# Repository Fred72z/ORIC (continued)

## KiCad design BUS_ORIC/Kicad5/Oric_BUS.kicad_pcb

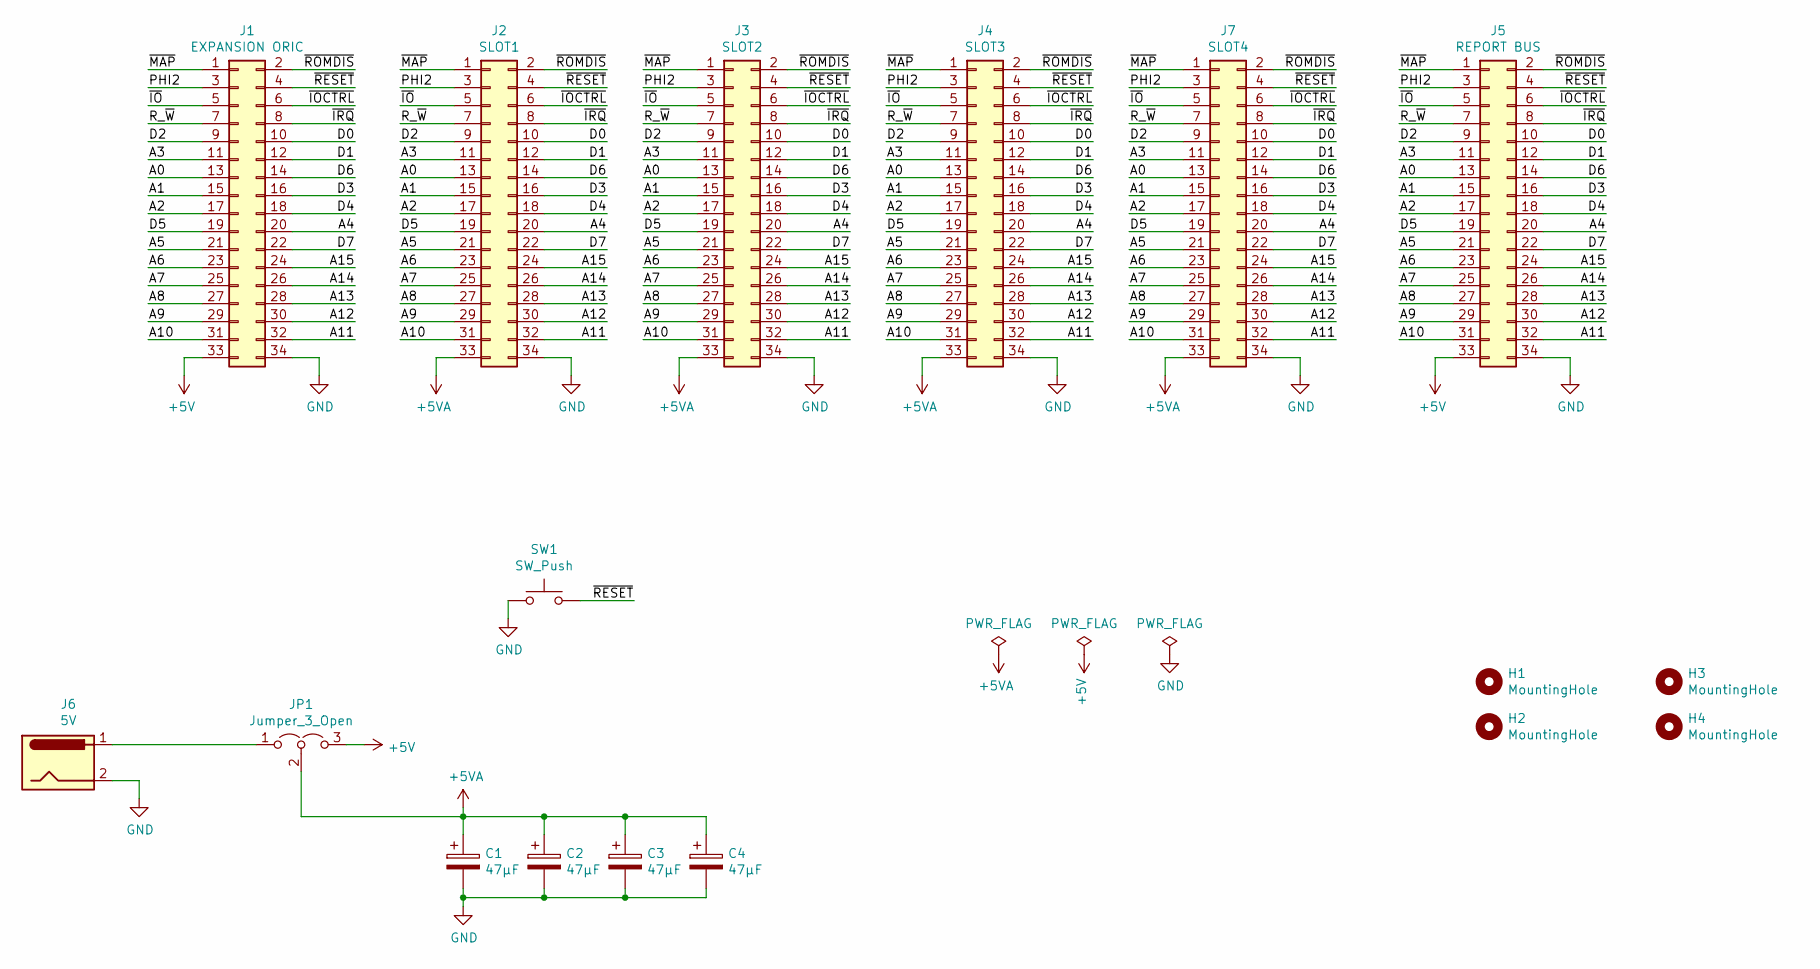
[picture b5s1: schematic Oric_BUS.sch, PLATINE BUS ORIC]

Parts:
C1, C2, C3, C4: 47µF; CP_Radial_D5.0mm_P2.00mm_Horizontal
H1, H2, H3, H4: MountingHole; MountingHole_3.2mm_M3
J1: EXPANSION ORIC; IDC-Header_2x17_P2.54mm_Vertical
J2: SLOT1; PinSocket_2x17_P2.54mm_Vertical
J3: SLOT2; PinSocket_2x17_P2.54mm_Vertical
J4: SLOT3; PinSocket_2x17_P2.54mm_Vertical
J5: REPORT BUS; IDC-Header_2x17_P2.54mm_Vertical
J6: 5V; BarrelJack_Horizontal
J7: SLOT4; PinSocket_2x17_P2.54mm_Vertical
JP1: Jumper_3_Open; PinHeader_1x03_P2.54mm_Vertical
SW1: SW_Push; SW_Tactile_SPST_Angled_PTS645Vx39-2LFS

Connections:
+5V: J1.33, J5.33, JP1.3 (B)
+5VA: C1.1, C2.1, C3.1, C4.1, J2.33, J3.33, J4.33, J7.33, JP1.2 (C)
/A0: J1.13, J2.13, J3.13, J4.13, J5.13, J7.13
/A1: J1.15, J2.15, J3.15, J4.15, J5.15, J7.15
/A2: J1.17, J2.17, J3.17, J4.17, J5.17, J7.17
/A3: J1.11, J2.11, J3.11, J4.11, J5.11, J7.11
/A4: J1.20, J2.20, J3.20, J4.20, J5.20, J7.20
/A5: J1.21, J2.21, J3.21, J4.21, J5.21, J7.21
/A6: J1.23, J2.23, J3.23, J4.23, J5.23, J7.23
/A7: J1.25, J2.25, J3.25, J4.25, J5.25, J7.25
/A8: J1.27, J2.27, J3.27, J4.27, J5.27, J7.27
/A9: J1.29, J2.29, J3.29, J4.29, J5.29, J7.29
/A10: J1.31, J2.31, J3.31, J4.31, J5.31, J7.31
/A11: J1.32, J2.32, J3.32, J4.32, J5.32, J7.32
/A12: J1.30, J2.30, J3.30, J4.30, J5.30, J7.30
/A13: J1.28, J2.28, J3.28, J4.28, J5.28, J7.28
/A14: J1.26, J2.26, J3.26, J4.26, J5.26, J7.26
/A15: J1.24, J2.24, J3.24, J4.24, J5.24, J7.24
/D0: J1.10, J2.10, J3.10, J4.10, J5.10, J7.10
/D1: J1.12, J2.12, J3.12, J4.12, J5.12, J7.12
/D2: J1.9, J2.9, J3.9, J4.9, J5.9, J7.9
/D3: J1.16, J2.16, J3.16, J4.16, J5.16, J7.16
/D4: J1.18, J2.18, J3.18, J4.18, J5.18, J7.18
/D5: J1.19, J2.19, J3.19, J4.19, J5.19, J7.19
/D6: J1.14, J2.14, J3.14, J4.14, J5.14, J7.14
/D7: J1.22, J2.22, J3.22, J4.22, J5.22, J7.22
/PHI2: J1.3, J2.3, J3.3, J4.3, J5.3, J7.3
/R_~W: J1.7, J2.7, J3.7, J4.7, J5.7, J7.7
/~IO: J1.5, J2.5, J3.5, J4.5, J5.5, J7.5
/~IOCTRL: J1.6, J2.6, J3.6, J4.6, J5.6, J7.6
/~IRQ: J1.8, J2.8, J3.8, J4.8, J5.8, J7.8
/~MAP: J1.1, J2.1, J3.1, J4.1, J5.1, J7.1
/~RESET: J1.4, J2.4, J3.4, J4.4, J5.4, J7.4, SW1.2
/~ROMDIS: J1.2, J2.2, J3.2, J4.2, J5.2, J7.2
GND: C1.2, C2.2, C3.2, C4.2, J1.34, J2.34, J3.34, J4.34, J5.34, J6.2, J7.34, SW1.1
unnamed: J6.1, JP1.1 (A)

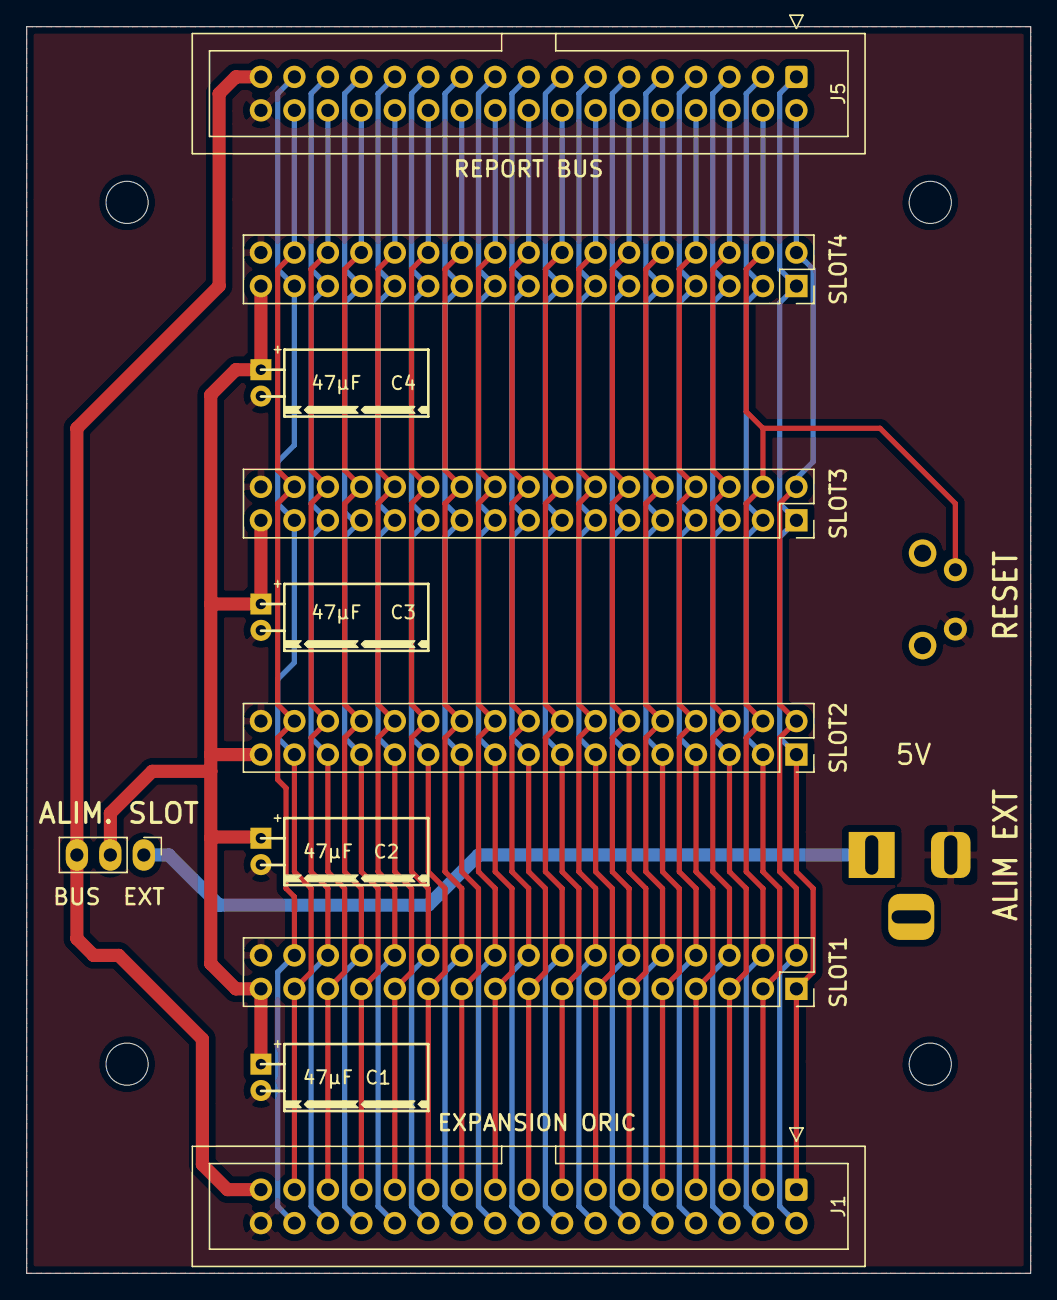
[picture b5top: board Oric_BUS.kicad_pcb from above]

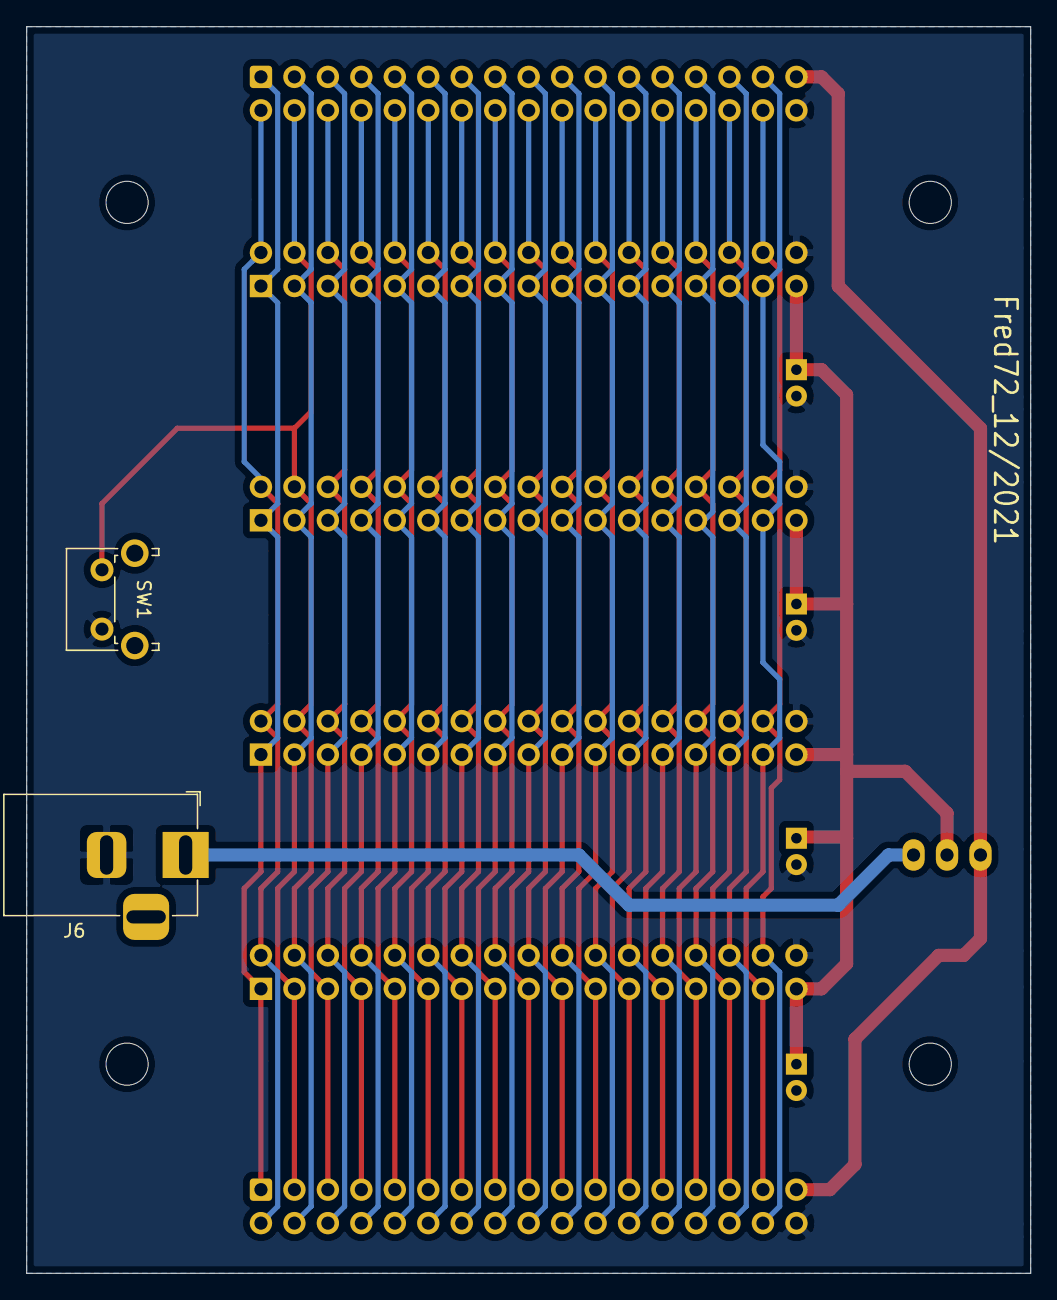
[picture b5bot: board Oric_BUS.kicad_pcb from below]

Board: 2 copper layers, 76.2 x 94.6 mm, 17 parts (2 on the bottom side), 36 nets.

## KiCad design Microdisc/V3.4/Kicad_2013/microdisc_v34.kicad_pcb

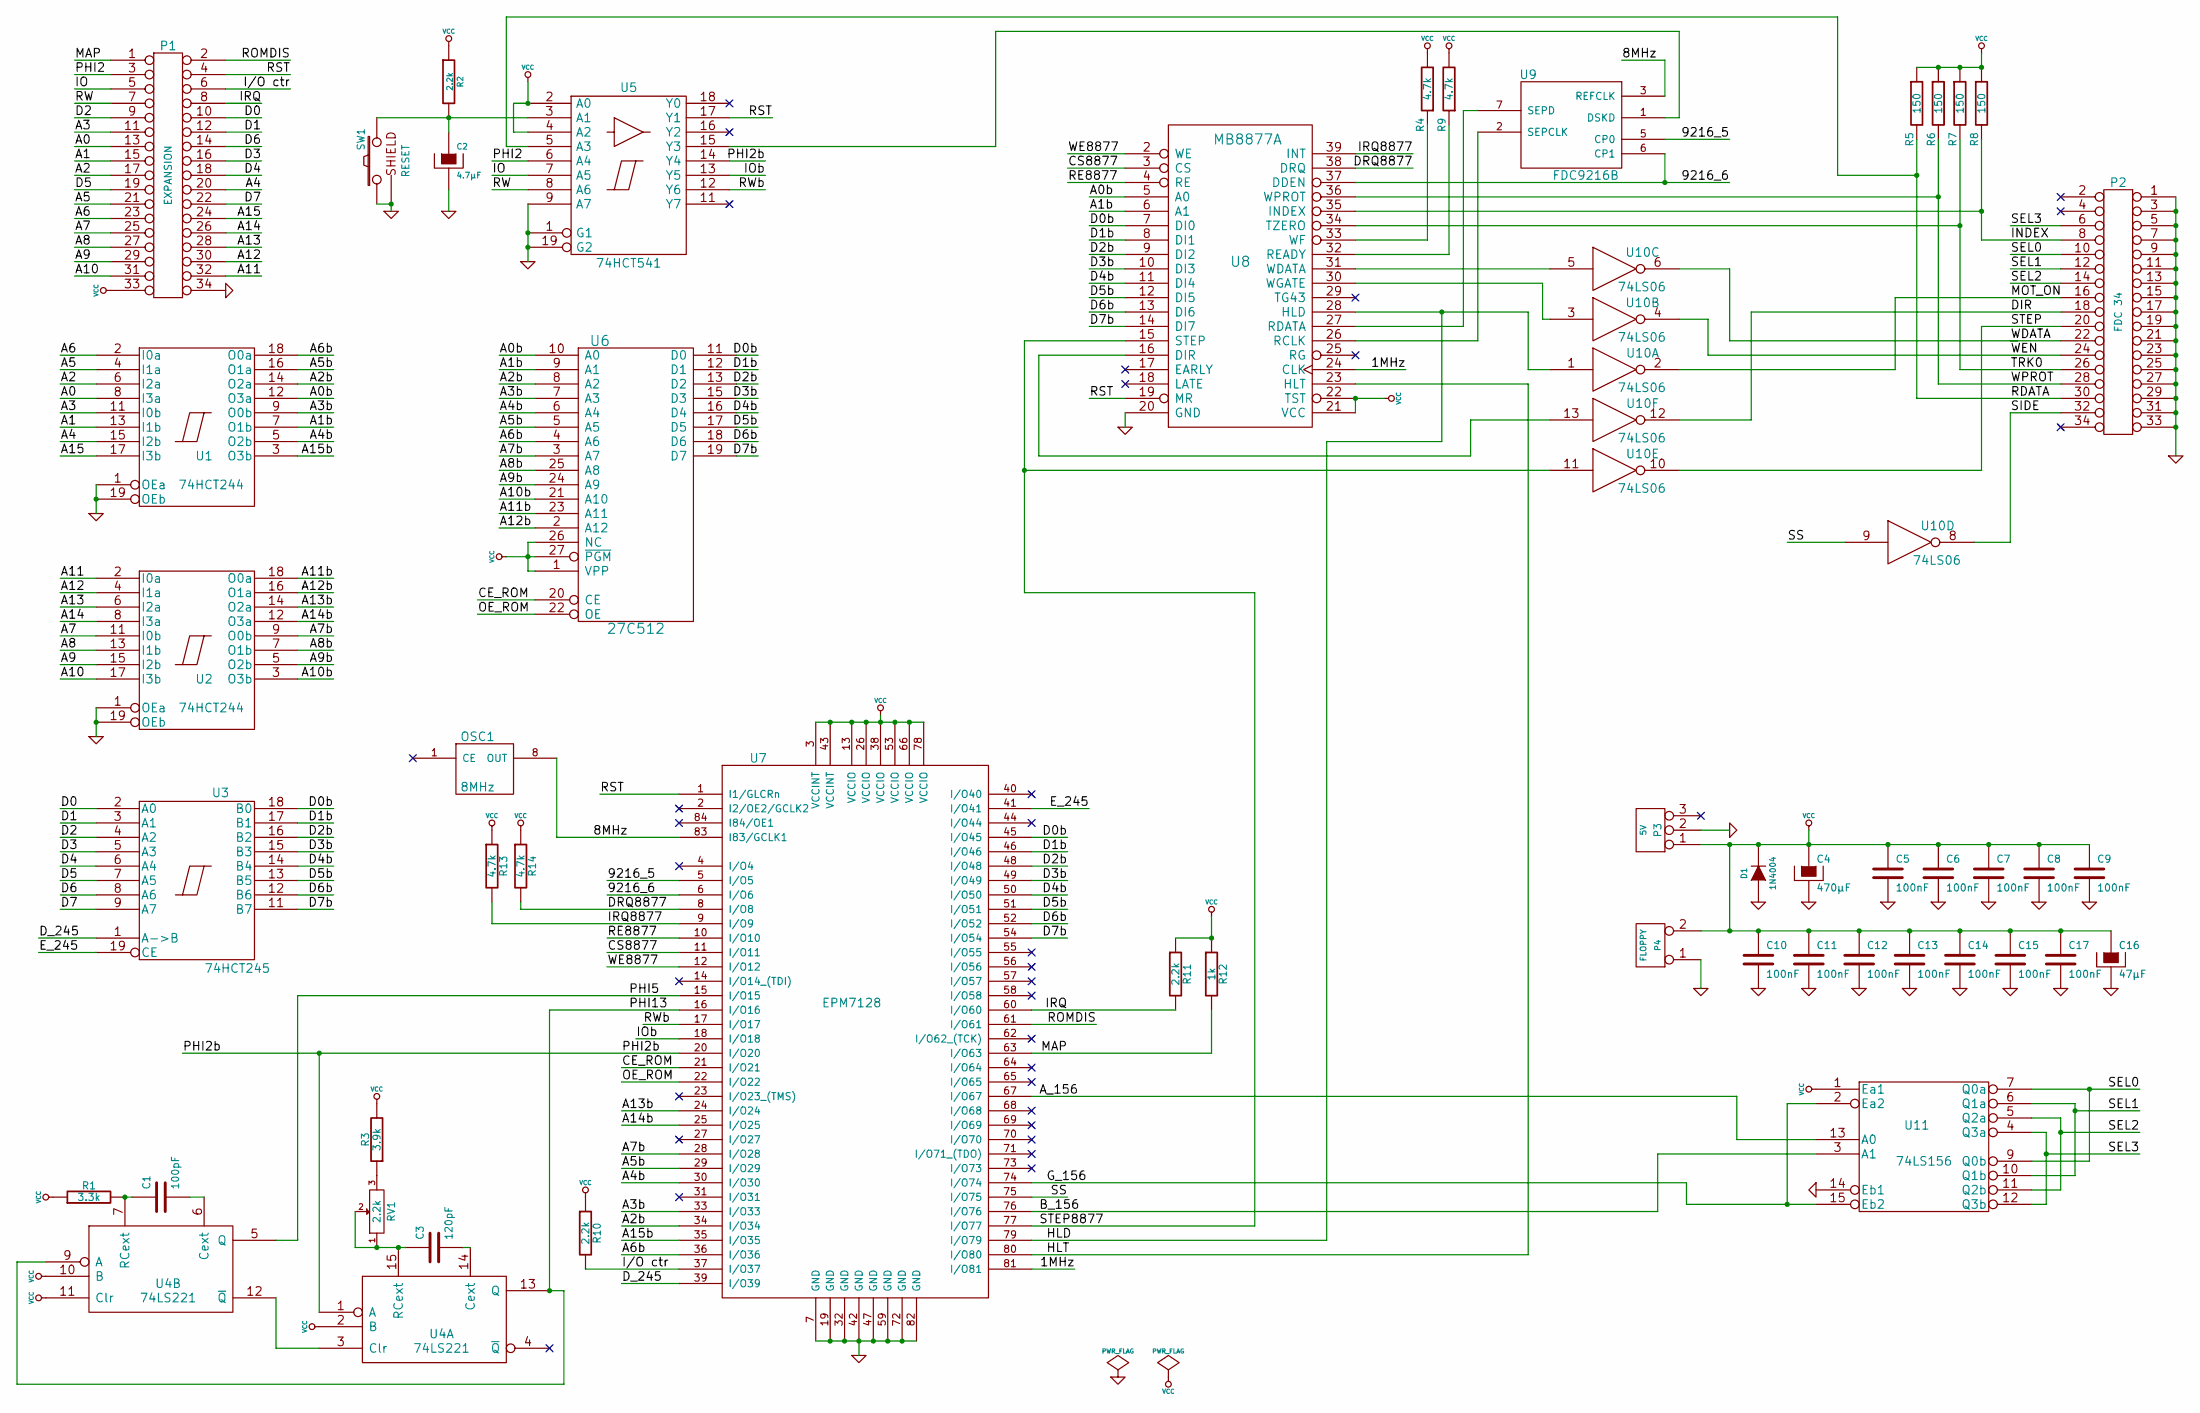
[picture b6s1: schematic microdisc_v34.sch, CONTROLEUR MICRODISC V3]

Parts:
C1: 100pF
C2: 4.7µF
C3: 120pF
C4: 470µF
C5, C6, C7, C8, C9, C10, C11, C12, C13, C14, C15, C17: 100nF
C16: 47µF
D1: 1N4004
OSC1: 8MHz
P1: EXPANSION
P2: FDC 34
P3: 5V
P4: FLOPPY
R1: 3.3k
R2, R10, R11: 2.2k
R3: 3.9k
R4, R9, R13, R14: 4.7k
R5, R6, R7, R8: 150
R12: 1k
RV1: 2.2k
SW1: RESET
U1, U2: 74HCT244
U3: 74HCT245
U4: 74LS221
U5: 74HCT541
U6: 27C512
U7: EPM7128
U8: MB8877A
U9: FDC9216B
U10: 74LS06
U11: 74LS156

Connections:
/1MHz: U7.81 (I/O81), U8.24 (CLK)
/8MHz: OSC1.8 (OUT), U7.83 (I83/GCLK1), U9.3 (REFCLK)
/9216_5: U7.5 (I/O5), U9.5 (CP0)
/9216_6: U7.6 (I/O6), U8.37 (DDEN), U9.6 (CP1)
/A0: P1.13, U1.8 (I3a)
/A0b: U1.12 (O3a), U6.10 (A0), U8.5 (A0)
/A1: P1.15, U1.13 (I1b)
/A1b: U1.7 (O1b), U6.9 (A1), U8.6 (A1)
/A2: P1.17, U1.6 (I2a)
/A2b: U1.14 (O2a), U6.8 (A2), U7.34 (I/O34)
/A3: P1.11, U1.11 (I0b)
/A3b: U1.9 (O0b), U6.7 (A3), U7.33 (I/O33)
/A4: P1.20, U1.15 (I2b)
/A4b: U1.5 (O2b), U6.6 (A4), U7.30 (I/O30)
/A5: P1.21, U1.4 (I1a)
/A5b: U1.16 (O1a), U6.5 (A5), U7.29 (I/O29)
/A6: P1.23, U1.2 (I0a)
/A6b: U1.18 (O0a), U6.4 (A6), U7.36 (I/O36)
/A7: P1.25, U2.11 (I0b)
/A7b: U2.9 (O0b), U6.3 (A7), U7.28 (I/O28)
/A8: P1.27, U2.13 (I1b)
/A8b: U2.7 (O1b), U6.25 (A8)
/A9: P1.29, U2.15 (I2b)
/A9b: U2.5 (O2b), U6.24 (A9)
/A10: P1.31, U2.17 (I3b)
/A10b: U2.3 (O3b), U6.21 (A10)
/A11: P1.32, U2.2 (I0a)
/A11b: U2.18 (O0a), U6.23 (A11)
/A12: P1.30, U2.4 (I1a)
/A12b: U2.16 (O1a), U6.2 (A12)
/A13: P1.28, U2.6 (I2a)
/A13b: U2.14 (O2a), U7.24 (I/O24)
/A14: P1.26, U2.8 (I3a)
/A14b: U2.12 (O3a), U7.25 (I/O25)
/A15: P1.24, U1.17 (I3b)
/A15b: U1.3 (O3b), U7.35 (I/O35)
/A_156: U7.67 (I/O67), U11.13 (A0)
/B_156: U7.76 (I/O76), U11.3 (A1)
/CE_ROM: U6.20 (CE), U7.21 (I/O21)
/CS8877: U7.11 (I/O11), U8.3 (CS)
/D0: P1.10, U3.2 (A0)
/D0b: U3.18 (B0), U6.11 (D0), U7.45 (I/O45), U8.7 (DI0)
/D1: P1.12, U3.3 (A1)
/D1b: U3.17 (B1), U6.12 (D1), U7.46 (I/O46), U8.8 (DI1)
/D2: P1.9, U3.4 (A2)
/D2b: U3.16 (B2), U6.13 (D2), U7.48 (I/O48), U8.9 (DI2)
/D3: P1.16, U3.5 (A3)
/D3b: U3.15 (B3), U6.15 (D3), U7.49 (I/O49), U8.10 (DI3)
/D4: P1.18, U3.6 (A4)
/D4b: U3.14 (B4), U6.16 (D4), U7.50 (I/O50), U8.11 (DI4)
/D5: P1.19, U3.7 (A5)
/D5b: U3.13 (B5), U6.17 (D5), U7.51 (I/O51), U8.12 (DI5)
/D6: P1.14, U3.8 (A6)
/D6b: U3.12 (B6), U6.18 (D6), U7.52 (I/O52), U8.13 (DI6)
/D7: P1.22, U3.9 (A7)
/D7b: U3.11 (B7), U6.19 (D7), U7.54 (I/O54), U8.14 (DI7)
/DIR: P2.18, U10.12
/DRQ8877: R14.2, U7.8 (I/O8), U8.38 (DRQ)
/D_245: U3.1 (A->B), U7.39 (I/O39)
/E_245: U3.19 (CE), U7.41 (I/O41)
/G_156: U7.74 (I/O74), U11.2 (Ea2), U11.15 (Eb2)
/HLD: U7.79 (I/O79), U8.28 (HLD), U10.1
/HLT: U7.80 (I/O80), U8.23 (HLT)
/I/O ctr: P1.6, R10.2, U7.37 (I/O37)
/INDEX: P2.8, R8.2, U8.35 (INDEX)
/IO: P1.5, U5.7 (A5)
/IOb: U5.13 (Y5), U7.18 (I/O18)
/IRQ: P1.8, R11.2, U7.60 (I/O60)
/IRQ8877: R13.2, U7.9 (I/O9), U8.39 (INT)
/MAP: P1.1, R12.2, U7.63 (I/O63)
/MOT_ON: P2.16, U10.2
/OE_ROM: U6.22 (OE), U7.22 (I/O22)
/PHI2: P1.3, U5.6 (A4)
/PHI2b: U4.1 (A), U5.14 (Y4), U7.20 (I/O20)
/PHI5: U4.5 (Q), U7.15 (I/O15)
/PHI13: U4.9 (A), U4.13 (Q), U7.16 (I/O16)
/RDATA: P2.30, R5.2, U5.5 (A3)
/RE8877: U7.10 (I/O10), U8.4 (RE)
/ROMDIS: P1.2, U7.61 (I/O61)
/RST: P1.4, U5.17 (Y1), U7.1 (I1/GLCRn), U8.19 (MR)
/RW: P1.7, U5.8 (A6)
/RWb: U5.12 (Y6), U7.17 (I/O17)
/SEL0: P2.10, U11.7 (Q0a), U11.9 (Q0b)
/SEL1: P2.12, U11.6 (Q1a), U11.10 (Q1b)
/SEL2: P2.14, U11.5 (Q2a), U11.11 (Q2b)
/SEL3: P2.6, U11.4 (Q3a), U11.12 (Q3b)
/SIDE: P2.32, U10.8
/SS: U7.75 (I/O75), U10.9
/STEP: P2.20, U10.10
/STEP8877: U7.77 (I/O77), U8.15 (STEP), U10.11
/TRK0: P2.26, R7.2, U8.34 (TZERO)
/WDATA: P2.22, U10.6
/WE8877: U7.12 (I/O12), U8.2 (WE)
/WEN: P2.24, U10.4
/WPROT: P2.28, R6.2, U8.36 (WPROT)
GND: C2.2, C4.2, C5.2, C6.2, C7.2, C8.2, C9.2, C10.2, C11.2, C12.2, C13.2, C14.2, C15.2, C16.2, C17.2, D1.1 (A), OSC1.7 (GND), P1.34, P2.1, P2.3, P2.5, P2.7, P2.9, P2.11, P2.13, P2.15, P2.17, P2.19, P2.21, P2.23, P2.25, P2.27, P2.29, P2.31, P2.33, P3.2 (PM), P4.1, SW1.1, SW1.3, U1.1 (OEa), U1.10 (GND), U1.19 (OEb), U2.1 (OEa), U2.10 (GND), U2.19 (OEb), U3.10 (GND), U4.8 (GND), U5.1 (G1), U5.9 (A7), U5.10 (GND), U5.19 (G2), U6.14 (GND), U7.7 (GND), U7.19 (GND), U7.32 (GND), U7.42 (GND), U7.47 (GND), U7.59 (GND), U7.72 (GND), U7.82 (GND), U8.20 (GND), U9.4 (GND), U10.7 (GND), U11.8 (GND), U11.14 (Eb1)
unnamed: U5.15 (Y3), U9.1 (DSKD)
unnamed: C2.1, R2.2, SW1.2, U5.3 (A1)
unnamed: R3.1, RV1.3
unnamed: C3.2, U4.14 (Cext)
unnamed: U8.27 (RDATA), U9.7 (SEPD)
unnamed: U8.26 (RCLK), U9.2 (SEPCLK)
unnamed: U8.16 (DIR), U10.13
unnamed: C1.1, R1.2, U4.7 (RCext)
unnamed: C1.2, U4.6 (Cext)
unnamed: U4.3 (Clr), U4.12 (~Q)
unnamed: C3.1, RV1.1, RV1.2, U4.15 (RCext)
unnamed: R4.1, U8.33 (WF)
unnamed: R9.1, U8.32 (READY)
unnamed: U8.31 (WDATA), U10.5
unnamed: U8.30 (WGATE), U10.3
VCC: C4.1, C5.1, C6.1, C7.1, C8.1, C9.1, C10.1, C11.1, C12.1, C13.1, C14.1, C15.1, C16.1, C17.1, D1.2 (K), OSC1.14 (VCC), P1.33, P3.1, P4.2 (PM), R1.1, R2.1, R3.2, R4.2, R5.1, R6.1, R7.1, R8.1, R9.2, R10.1, R11.1, R12.1, R13.1, R14.1, U1.20 (VCC), U2.20 (VCC), U3.20 (VCC), U4.2 (B), U4.10 (B), U4.11 (Clr), U4.16 (VCC), U5.2 (A0), U5.4 (A2), U5.20 (VCC), U6.1 (VPP), U6.26 (NC), U6.27 (~PGM), U6.28 (VCC), U7.3 (VCCINT), U7.13 (VCCIO), U7.26 (VCCIO), U7.38 (VCCIO), U7.43 (VCCINT), U7.53 (VCCIO), U7.66 (VCCIO), U7.78 (VCCIO), U8.21 (VCC), U8.22 (TST), U9.8 (VCC), U10.14 (VCC), U11.1 (Ea1), U11.16 (VCC)

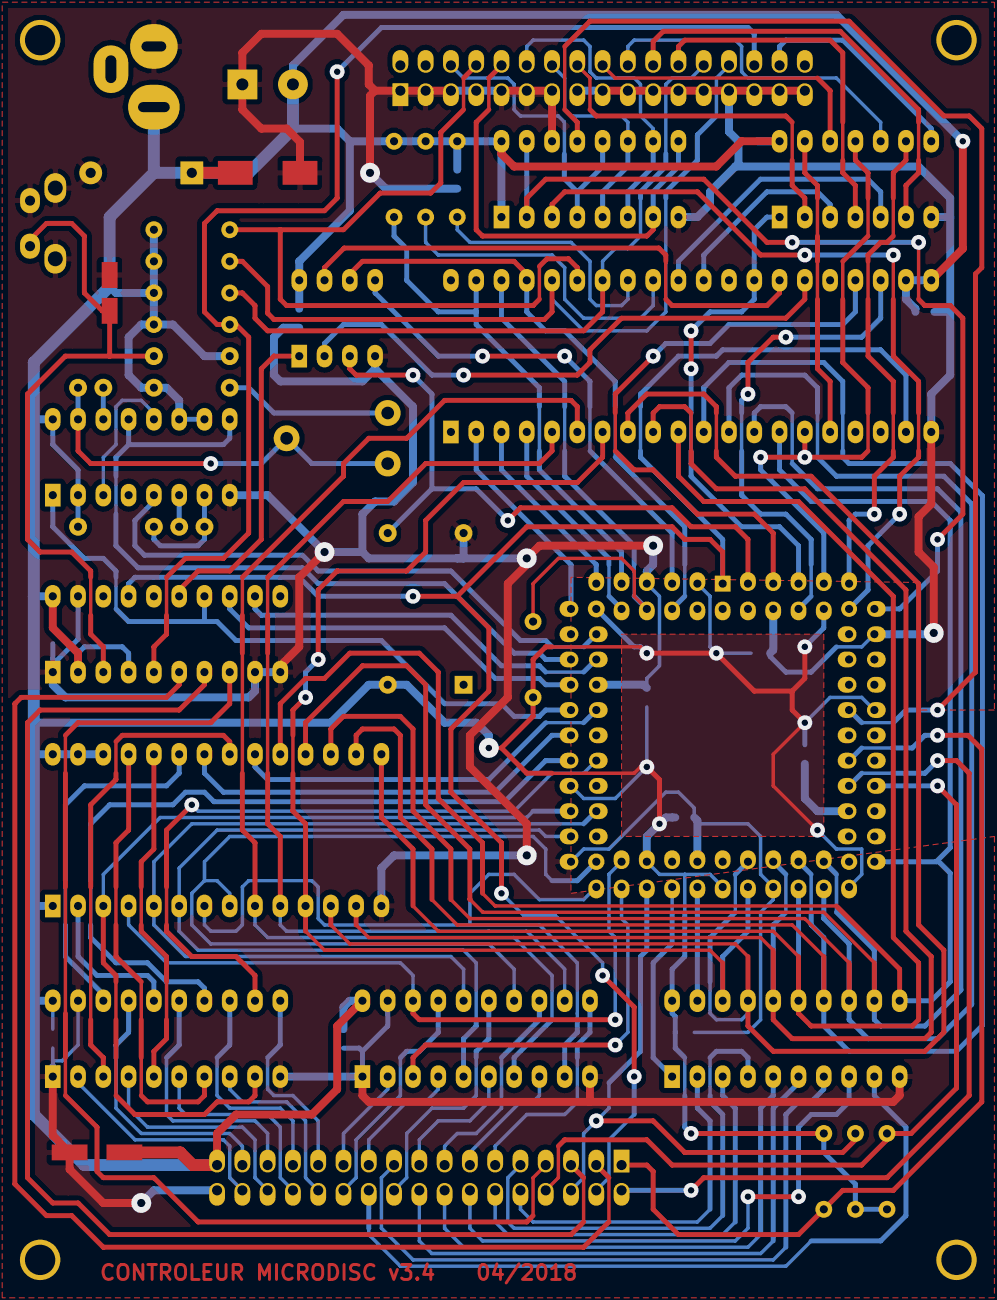
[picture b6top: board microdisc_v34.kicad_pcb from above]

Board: 2 copper layers, 54 parts (0 on the bottom side), 112 nets.

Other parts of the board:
1PIN, 1PIN#2, 1PIN#3, 1PIN#4: P***; 1pin
